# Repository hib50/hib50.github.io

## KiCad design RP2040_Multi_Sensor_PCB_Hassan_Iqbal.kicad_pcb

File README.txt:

# EcoBright Phase 1 portfolio page

Upload these items into your `hib50.github.io` repository preserving the paths:

- `projects/ecobright-phase1.html`
- `assets/images/ecobright-phase1/*`

The HTML already links to `../style.css`, so it will use your existing site styling plus page-specific styles embedded in the page.

The full confidential validation report is intentionally **not** included.

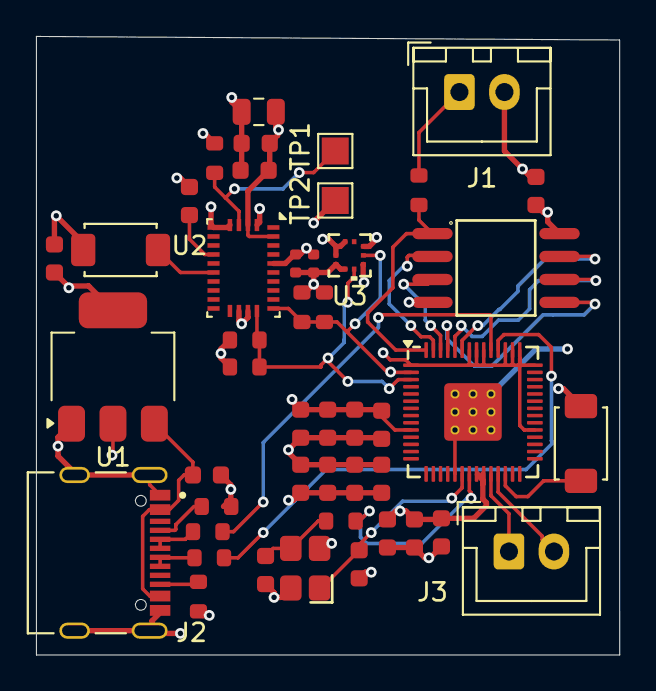
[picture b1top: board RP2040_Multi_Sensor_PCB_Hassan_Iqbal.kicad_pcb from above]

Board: 4 copper layers, 32.4 x 34.4 mm, 46 parts (0 on the bottom side), 27 nets.

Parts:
C2, C4, C6, C7, C8, C9, C10, C11, C12, C16, C17, C19: 100nF; C_0603
C3: 120nF; C_0805_2012Metric
C5: 6.8nF; C_0603
C13, C18: 1uF; C_0603
C14, C15: 10uF; C_0603
C20, C21: 30pF; C_0603
C22, C23: 100nF; C_0402
J1, J3: Conn_01x02; JST_XH_B2B-XH-A_1x02_P2.50mm_Vertical
J2: TYPE-C-31-M-12; HRO_TYPE-C-31-M-12
R2, R3, R6: 10kΩ; R_0603
R7, R8: 5.1kΩ; R_0603
R9, R10: 27Ω; R_0603
R11, R14: 4.7kΩ; R_0603
R12, R13: 1kΩ; R_0603
S1, S2: Tactile Button, 160gf; SW_TS-1088-AR02016
TP1, TP2: TestPoint; TestPoint_Pad_1.5x1.5mm
U1: AMS1117; SOT-223-3_TabPin2
U2: BNO055; LGA-28_5.2x3.8mm_P0.5mm
U3: BMP388; QFN_BMP388_BOS
U4: RP2040; QFN-56-1EP_7x7mm_P0.4mm_EP3.2x3.2mm_ThermalVias
U5: W25Q128; SOIC-8_L5.3-W5.3-P1.27-LS8.0-BL
X1: X322512MSB4SI; CRYSTAL-SMD_4P-L3.2-W2.5-BL

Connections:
+3.3V: C2.2, C3.1, C5.1, C6.1, C7.1, C8.1, C9.1, C10.1, C11.1, C12.1, C13.1, C14.1, C16.1, C17.1, C18.2, C19.1, C22.1, C23.1, R2.1, R3.1, R6.1, R11.1, R14.1, U1.2 (VOUT), U2.3 (VDD), U2.28 (VDDIO), U3.1 (VDDIO), U3.10 (VDD), U4.1 (IOVDD), U4.10 (IOVDD), U4.22 (IOVDD), U4.23 (DVDD), U4.33 (IOVDD), U4.42 (IOVDD), U4.43 (ADC_AVDD), U4.44 (VREG_IN), U4.45 (VREG_VOUT), U4.48 (USB_VDD), U4.49 (IOVDD), U4.50 (DVDD), U5.8 (VCC)
/DN1: J2.A7 (DN1), J2.B6 (DP2), R10.1
/DP1: J2.A6 (DP1), J2.B7 (DN2), R9.1
/QSPI_SCLK: U4.52 (QSPI_SCLK), U5.6 (CLK)
/QSPI_SD0: U4.53 (QSPI_SD0), U5.5 (DI)
/QSPI_SD1: U4.55 (QSPI_SD1), U5.2 (DO)
/QSPI_SD2: U4.54 (QSPI_SD2), U5.3 (IO2)
/QSPI_SD3: U4.51 (QSPI_SD3), U5.7 (IO3)
/QSPI_SS: R12.2, U4.56 (QSPI_SS), U5.1 (CS#)
/RESET: S1.2 (B), U2.11 (~RESET)
/RUN: S2.2 (B), U4.26 (RUN)
/SCL0: R6.2, R14.2, U2.19 (COM1), U3.2 (SCK), U4.3 (GPIO1)
/SDA0: R3.2, R11.2, U2.20 (COM0), U3.4 (SDI), U4.2 (GPIO0)
/VBUS: C15.1, J2.A4_B9 (VBUS), J2.B4_A9 (VBUS), U1.3 (VIN)
/XIN: C20.1, U4.20 (XIN), X1.1 (OSC)
/XOUT: R13.2, U4.21 (XOUT)
GND: C2.1, C3.2, C4.2, C5.2, C6.2, C7.2, C8.2, C9.2, C10.2, C11.2, C12.2, C13.2, C14.2, C15.2, C16.2, C17.2, C18.1, C19.2, C20.2, C21.1, C22.2, C23.2, J1.2, J2.A1_B12 (GND), J2.B1_A12 (GND), J2.S1 (SHIELD), J2.S2 (SHIELD), J2.S3 (SHIELD), J2.S4 (SHIELD), R7.2, R8.1, S1.1 (A), S2.1 (A), TP2.1, U1.1 (GND), U2.2 (GND), U2.5 (PS1), U2.6 (PS0), U2.17 (COM3), U2.18 (COM2), U2.25 (GNDIO), U3.3 (VSS), U3.5 (SDO), U3.7 (INT), U3.8 (VSS), U3.9 (VSS), U4.19 (TESTEN), U4.57 (GND), U5.4 (GND), X1.2 (GND), X1.4 (GND)
unnamed: C21.2, R13.1, X1.3 (OSC)
unnamed: J1.1, R12.1
unnamed: J2.A5 (CC1), R7.1
unnamed: J2.B5 (CC2), R8.2
unnamed: J3.1, U4.24 (SWCLK)
unnamed: J3.2, U4.25 (SWD)
unnamed: C4.1, U2.9 (CAP)
unnamed: R2.2, TP1.1, U2.4 (~BOOT_LOAD_PIN)
unnamed: R10.2, U4.46 (USB_DM)
unnamed: R9.2, U4.47 (USB_DP)
